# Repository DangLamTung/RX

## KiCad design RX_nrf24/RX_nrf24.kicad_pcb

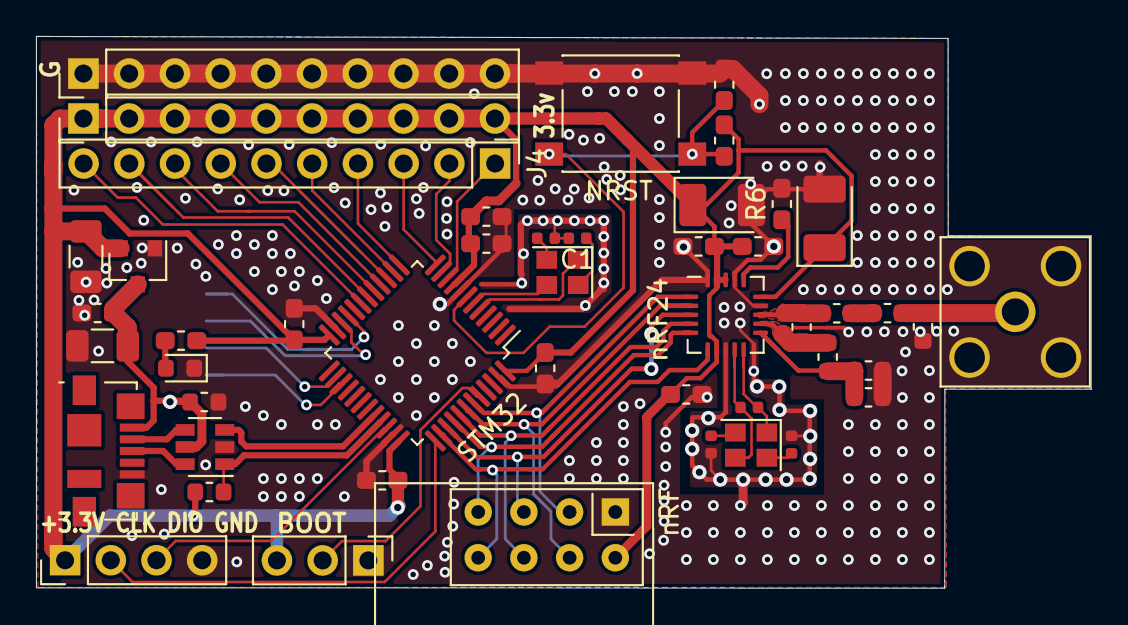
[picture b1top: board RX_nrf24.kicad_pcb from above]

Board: 2 copper layers, 58.6 x 30.7 mm, 48 parts (1 on the bottom side), 46 nets.

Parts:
1.5pF1, 1pF1, 1pF2, 1pF3: C; C_0603_1608Metric
2.7nH1, 3.9nH1, 8.2nH1: L; C_0603_1608Metric
3.3v: Conn_01x10_Male; PinHeader_1x10_P2.54mm_Vertical
+3.3V CLK DIO GND: Conn_01x04_Female; PinHeader_1x04_P2.54mm_Vertical
BOOT: Conn_01x03_Male; PinHeader_1x03_P2.54mm_Vertical
C1, C2, C20, C22: 18pF; C_0402_1005Metric
C3, C5, C6, C7, C8, C10, C11, C14, C15, C16: C; C_0603_1608Metric_Pad1.05x0.95mm_HandSolder
C4, C9: CP; C_1206_3216Metric
C12: C; CP_EIA-3528-12_Kemet-T_Pad1.50x2.35mm_HandSolder
C13: C; C_0603_1608Metric
C13#2: CP; CP_EIA-3528-12_Kemet-T_Pad1.50x2.35mm_HandSolder
D1: LED; LED_0603_1608Metric
G: Conn_01x10_Male; PinHeader_1x10_P2.54mm_Vertical
J1: USB_B_Micro; USB_Micro-B_Molex_47346-0001
J3: Conn_Coaxial; SMA_Amphenol_132203-12_Horizontal
J4: Conn_01x10_Male; PinHeader_1x10_P2.54mm_Vertical
J6: Conn_01x06_Male; JST_ZE_SM06B-ZESS-TB_1x06-1MP_P1.50mm_Horizontal
NRST: SW_Push; SW_Push_1P1T_NO_6x6mm_H9.5mm
R1: R; R_0603_1608Metric
R2, R3, R6: R; R_0603_1608Metric_Pad1.05x0.95mm_HandSolder
R7: 1M; R_0402_1005Metric
STM32: STM32F103C8Tx; LQFP-48_7x7mm_P0.5mm
U1: USBLC6-2SC6; SOT-23-6
U2: MCP1700-3302E_SOT23; SOT-23
Y1, Y2: Crystal_GND24; Crystal_SMD_2520-4Pin_2.5x2.0mm
nRF: NRF24L01_Breakout; nRF24L01_Breakout
nRF24: nRF24L01P; QFN-20-1EP_4x4mm_P0.5mm_EP2.5x2.5mm

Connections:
+3V3: 3.3v.1, 3.3v.2, 3.3v.3, 3.3v.4, 3.3v.5, 3.3v.6, 3.3v.7, 3.3v.8, 3.3v.9, 3.3v.10, +3.3V CLK DIO GND.1, BOOT.3, C6.1, C7.1, C8.1, C9.1, C10.1, C11.1, C12.1, C13#2.1, C14.1, C15.1, C16.1, R1.2, R2.1, R3.2, STM32.9, STM32.24, STM32.36, STM32.48, U2.2, nRF.2, nRF24.7, nRF24.15, nRF24.18, nRF24.19
+5V: C4.1, C5.1, C13.1, J1.1, J6.1, U1.5, U2.3
BOOT0: BOOT.2, STM32.44
CE: STM32.43, nRF.3, nRF24.1
CSN: STM32.42, nRF.4, nRF24.2
D+: J1.3, U1.6
D-: J1.2, U1.4
GND: 1pF1.2, 1pF2.2, 1pF3.2, +3.3V CLK DIO GND.4, BOOT.1, C1.2, C2.2, C3.2, C4.2, C5.2, C6.2, C7.2, C8.2, C9.2, C10.2, C11.2, C12.2, C13.2, C13#2.2, C14.2, C15.2, C16.2, C20.2, C22.2, D1.1, G.1, G.2, G.3, G.4, G.5, G.6, G.7, G.8, G.9, G.10, J1.5, J3.2, J6.6, NRST.1, R6.2, STM32.8, STM32.23, STM32.35, STM32.47, U1.2, U2.1, nRF.1, nRF24.8, nRF24.14, nRF24.17, nRF24.20
IRQ: STM32.38, nRF.8, nRF24.6
MISO: STM32.40, nRF.7, nRF24.5
MOSI: STM32.41, nRF.6, nRF24.4
NRST: C3.1, NRST.2, R2.2, STM32.7
unnamed: 1.5pF1.1, 3.9nH1.2
unnamed: 2.7nH1.1, 8.2nH1.2, nRF24.12
unnamed: 3.9nH1.1, 8.2nH1.1, nRF24.13
unnamed: C1.1, Y1.4
unnamed: C2.1, Y1.2
unnamed: C20.1, Y2.4
unnamed: C22.1, Y2.2
unnamed: D1.2, R3.1
unnamed: R6.1, nRF24.16
unnamed: R7.1, Y2.1, nRF24.10
unnamed: R7.2, Y2.3, nRF24.9
unnamed: STM32.5, Y1.1
unnamed: STM32.6, Y1.3
P1: J4.1, STM32.10
P2: J4.2, STM32.11
P3: J4.3, STM32.12
P4: J4.4, STM32.13
P5: J4.5, STM32.14
P6: J4.6, STM32.15
P7: J4.7, STM32.16
P8: J4.8, STM32.17
P9: J4.9, STM32.18
P10: J4.10, STM32.19
RF_out: 1.5pF1.2, 1pF2.1, J3.1
SCK: STM32.39, nRF.5, nRF24.3
SWCLK: +3.3V CLK DIO GND.2, STM32.37
SWDIO: +3.3V CLK DIO GND.3, STM32.34
TXEN: 1pF1.1, 1pF3.1, 2.7nH1.2, nRF24.11
UART3_CTS: J6.3, STM32.26
UART3_RTS: J6.2, STM32.27
UART3_RX: J6.4, STM32.22
UART3_TX: J6.5, STM32.21
USB_D+: R1.1, STM32.33, U1.1
USB_D-: STM32.32, U1.3

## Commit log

2020-08-12 add alot
2020-08-14 update pcb
2020-08-20 layout
2020-08-20 a
    a
2020-08-20 rf layout
2020-08-21 rf layout:
2020-08-21 addd
2020-09-21 add bao cao
2020-09-23 bao cao
